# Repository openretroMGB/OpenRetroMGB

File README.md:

> Get ready to elevate your retro gaming experience with **OpenretroMGB** - the open-source, modular gaming board that lets you customize your gameplay. Our upcoming campaign will offer exclusive rewards and perks, so don't miss out on your chance to join the retro gaming revolution. Stay tuned for more details and be part of the community that's bringing back the best of the past with the power of the future!

## Overview

**OpenretroMGB** is a new open-source ***M***odular ***G***aming ***B***oard designed for gamers and hobbyists alike. Based on the popular Retro ESP32, this compact and portable board is compatible with Game Boy Pocket form factor and allows customers to either use the prebuilt ESP32 cartridge or design their own. With an easy-to-use modular design, gamers can customize their gaming experience by swapping out cartridges that feature different games or hardware functionalities. OpenretroMGB offers an affordable and accessible way to create and enjoy retro-style games with modern features, making it perfect for enthusiasts, hobbyists, and anyone looking for a fun, retro gaming experience.

**OpenretroMGB** is certified unde Open Source Hardware as OSHWA UID [CA000028](https://certification.oshwa.org/ca000028.html) with CC-BY-SA-4.0 licensing

## Features
- [x] Cartridge slot
- [x] 2.6" daylight IPS screen
- [x] Volume and brightness control
- [x] LiPo battery charging and protection circuitry
- [x] Stereo chip and headphone jack
- [x] Drop-in compatibility with Game Boy Pocket shell
- [x] Modular design
- [x] USB Data Lines
- [x] Open source

### Have your say

Join our discussions. Cast your vote in our [polls](https://github.com/openretroMGB/OpenRetroMGB/discussions/categories/polls)

## Gallery

#### Retro ESP32 Cart

#### Arduino *ATmega32U4* Cart

#### USB C Data Lines

# What will you build?

## Trusted Creators
> Celebrating 10 Years

Over the past 10 years, we have proudly established ourselves as a trusted creator and innovator in the realm of handheld retro gaming. From our early ventures with Arduino and Atmega microcontrollers to our exploration of cutting-edge technologies like ESP32 and Raspberry Pi, our journey has been driven by a relentless pursuit of innovation. With each step, we have strived to enhance the gaming experience for retro enthusiasts. Our Game Boy Pocket PCB embodies our dedication to quality, reliability, and creativity. It represents a culmination of years of expertise, resulting in a product that seamlessly blends the nostalgia of classic gaming with the power and possibilities of modern technology. As we celebrate this milestone, we extend our gratitude to our loyal customers and supporters, who have played an instrumental role in our growth and success. Looking ahead, we remain committed to pushing boundaries, embracing new advancements, and delivering unforgettable gaming experiences to enthusiasts around the world.

## Authors

* **Eugene Yevhen Andruszczenko** - *Initial and Ongoing Work* - [32teeth](https://github.com/32teeth)

### License

This project is licensed under the Creative Commons Attribution Share Alike 4.0 International - see the [LICENSE.md](LICENSE.md) file for details

## Support
> Although we do this for 💕 of 🕹️<br/>
> **We Also Like Coffee!** <br/>
> *Please Consider Supporting* <br/>

Did you know, you can support us in a few way? We offer multiple sposorship tiers, with different rewards!

Take a *look*.
See what *fits*.

**Thank You**

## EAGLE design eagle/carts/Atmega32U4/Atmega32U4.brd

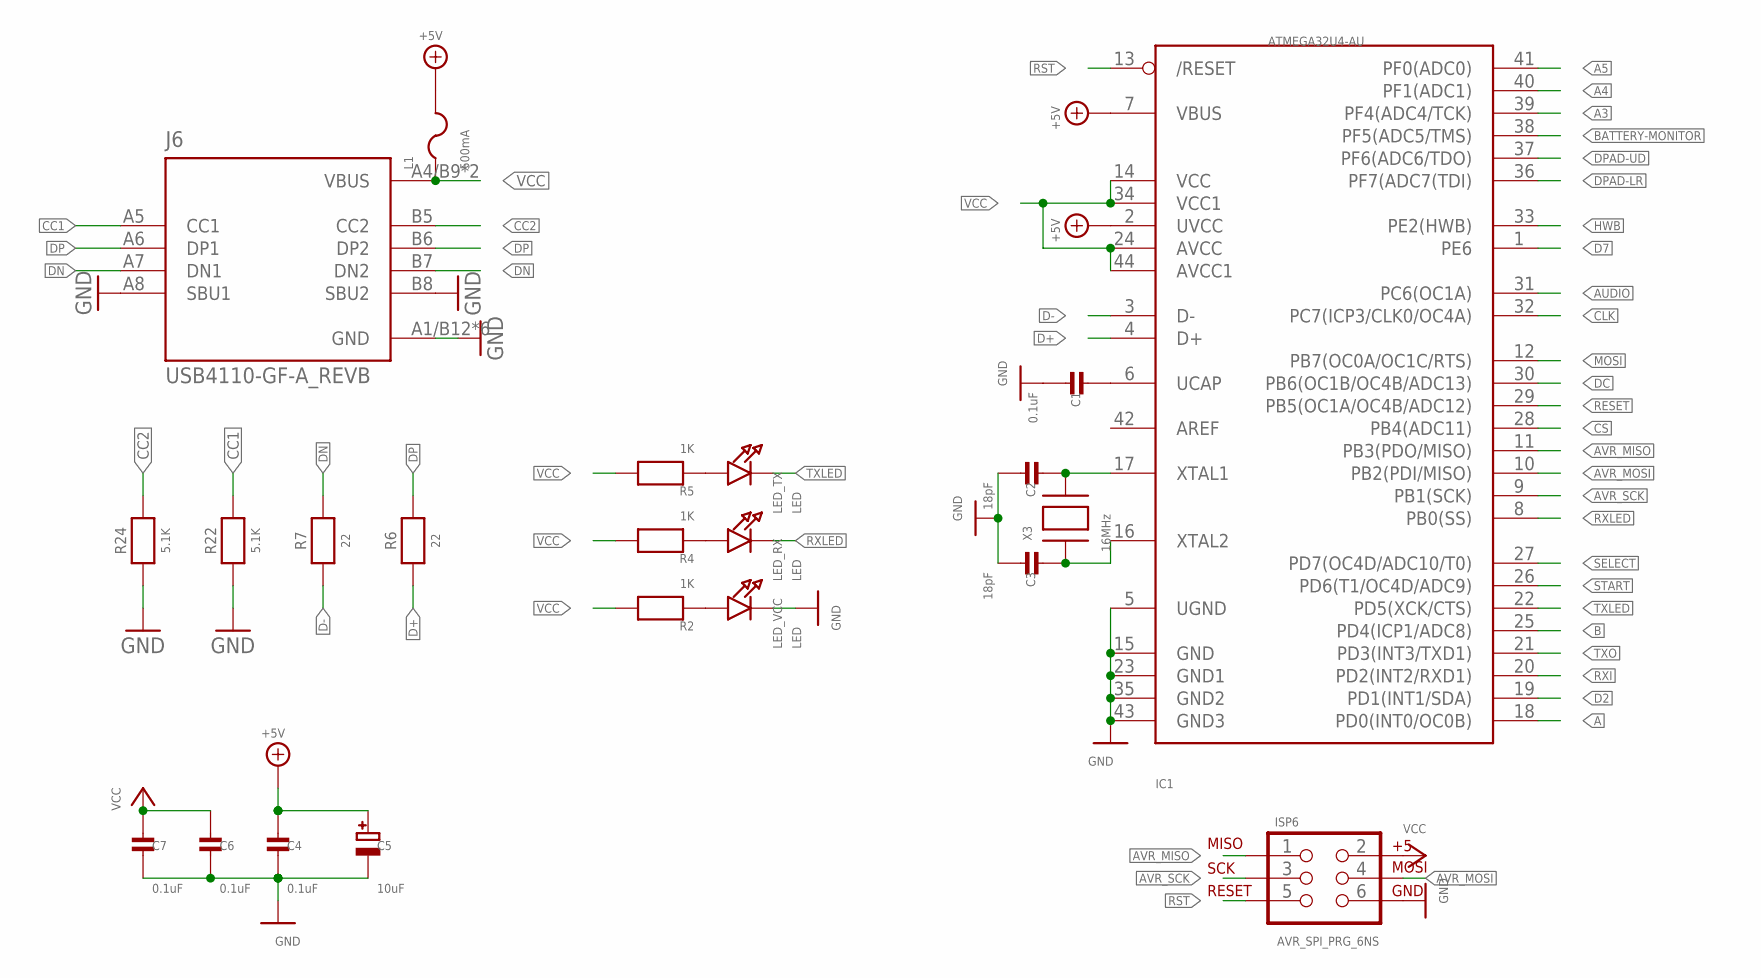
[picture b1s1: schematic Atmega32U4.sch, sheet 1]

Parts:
C1, C4, C6, C7: 0.1uF; 0603-MINI-CAP
C2, C3: 18pF; 0603-MINI-CAP
C5: 10uF; EIA3216-18/A-W
IC1: ATMEGA32U4-AU; TQFP44
ISP6: AVR_SPI_PRG_6NS; 2X3-NS
J6: USB4110-GF-A_REVB; GCT_USB4110-GF-A_REVB; MPN USB4105-GF-A
L1: 500mA; R1206
LED_RX: LED; CHIPLED_0603
LED_TX: LED; CHIPLED_0603
LED_VCC: LED; CHIPLED_0603
R2, R4, R5: 1K; 0603-MINI
R6, R7: 22; 0603-MINI; MPN ERJ-3EKF22R0V
R22, R24: 5.1K; 0603-MINI; MPN ERJ-PA3F5101V
X3: 16MHz; NX5032

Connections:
+5V: C4.1, C5.+, IC1.2 (UVCC), IC1.7 (VBUS), L1.2
A: IC1.18 (PD0(INT0/OC0B)); also elsewhere on the board
A3: IC1.39 (PF4(ADC4/TCK))
A4: IC1.40 (PF1(ADC1))
A5: IC1.41 (PF0(ADC0))
AUDIO: IC1.31 (PC6(OC1A)); also elsewhere on the board
AVR_MISO: IC1.11 (PB3(PDO/MISO)), ISP6.1
AVR_MOSI: IC1.10 (PB2(PDI/MISO)), ISP6.4
AVR_SCK: IC1.9 (PB1(SCK)), ISP6.3
B: IC1.25 (PD4(ICP1/ADC8)); also elsewhere on the board
BATTERY-MONITOR: IC1.38 (PF5(ADC5/TMS)); also elsewhere on the board
CC1: J6.A5 (CC1), R22.2
CC2: J6.B5 (CC2), R24.2
CLK: IC1.32 (PC7(ICP3/CLK0/OC4A)); also elsewhere on the board
CS: IC1.28 (PB4(ADC11)); also elsewhere on the board
D2: IC1.19 (PD1(INT1/SDA))
D7: IC1.1 (PE6)
D+: IC1.4 (D+), R6.1
D-: IC1.3 (D-), R7.1
DC: IC1.30 (PB6(OC1B/OC4B/ADC13)); also elsewhere on the board
DN: J6.A7 (DN1), J6.B7 (DN2), R7.2
DP: J6.A6 (DP1), J6.B6 (DP2), R6.2
DPAD-LR: IC1.36 (PF7(ADC7(TDI)); also elsewhere on the board
DPAD-UD: IC1.37 (PF6(ADC6/TDO)); also elsewhere on the board
GND: C1.2, C2.2, C3.2, C4.2, C5.-, C6.2, C7.2, IC1.5 (UGND), IC1.15 (GND), IC1.23 (GND1), IC1.35 (GND2), IC1.43 (GND3), ISP6.6, J6.A1/B12 (GND), J6.A8 (SBU1), J6.B1/A12 (GND), J6.B8 (SBU2), J6.S1 (GND), J6.S2 (GND), J6.S3 (GND), J6.S4 (GND), LED_VCC.C, R22.1, R24.1; also elsewhere on the board
HWB: IC1.33 (PE2(HWB))
MOSI: IC1.12 (PB7(OC0A/OC1C/RTS)); also elsewhere on the board
unnamed: LED_VCC.A, R2.1
unnamed: C1.1, IC1.6 (UCAP)
unnamed: LED_RX.A, R4.1
unnamed: LED_TX.A, R5.1
unnamed: C2.1, IC1.17 (XTAL1), X3.P$2
unnamed: C3.1, IC1.16 (XTAL2), X3.P$1
RESET: IC1.29 (PB5(OC1A/OC4B/ADC12)); also elsewhere on the board
RST: IC1.13 (/RESET), ISP6.5
RXI: IC1.20 (PD2(INT2/RXD1))
RXLED: IC1.8 (PB0(SS)), LED_RX.C
SELECT: IC1.27 (PD7(OC4D/ADC10/T0)); also elsewhere on the board
START: IC1.26 (PD6(T1/OC4D/ADC9)); also elsewhere on the board
TXLED: IC1.22 (PD5(XCK/CTS)), LED_TX.C
TXO: IC1.21 (PD3(INT3/TXD1))
VCC: C6.1, C7.1, IC1.14 (VCC), IC1.24 (AVCC), IC1.34 (VCC1), IC1.44 (AVCC1), ISP6.2, J6.A4/B9 (VBUS), J6.B4/A9 (VBUS), L1.1, R2.2, R4.2, R5.2; also elsewhere on the board

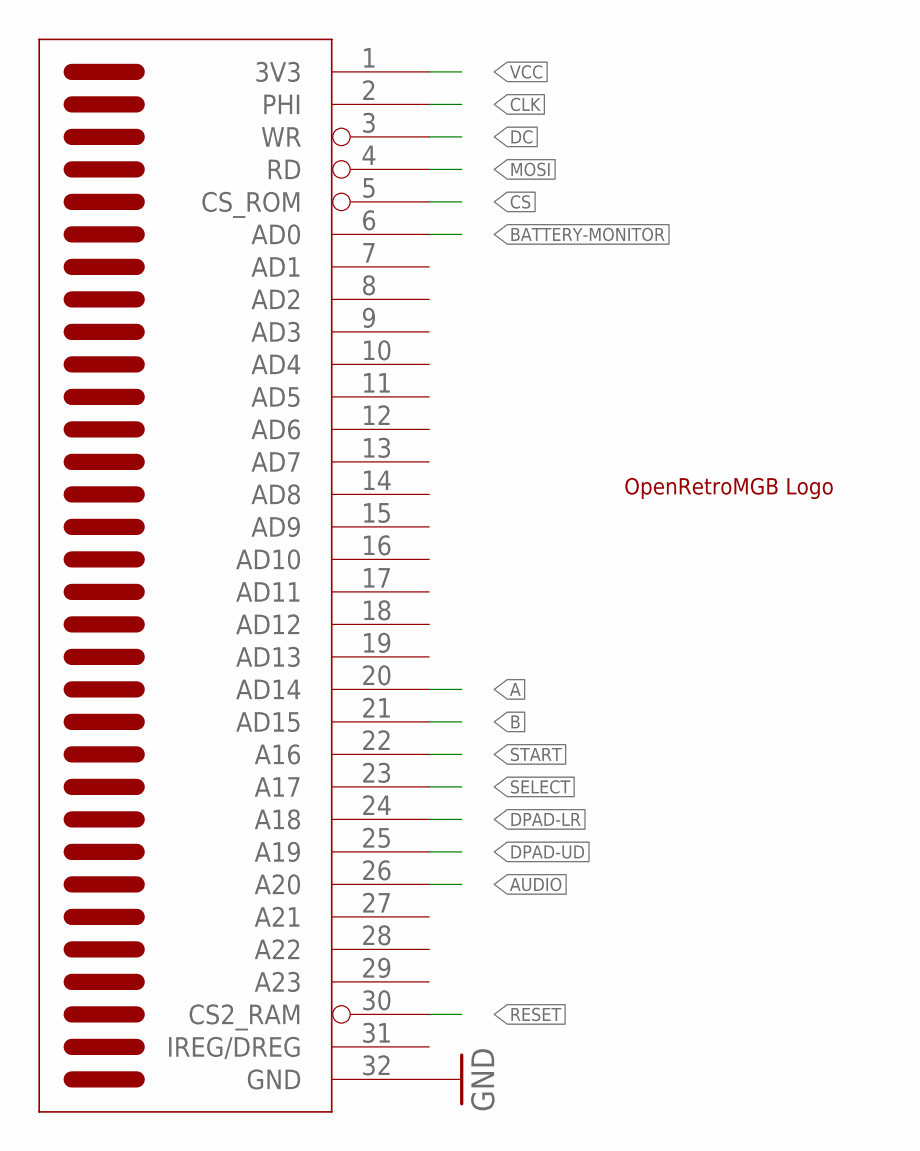
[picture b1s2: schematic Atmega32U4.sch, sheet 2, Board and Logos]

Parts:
U$1: OPENRETROMGB; OPENRETROMBG
U$2: GBA_CARTLARGE; GBCART

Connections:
A: U$2.20 (AD14); also elsewhere on the board
AUDIO: U$2.26 (A20); also elsewhere on the board
B: U$2.21 (AD15); also elsewhere on the board
BATTERY-MONITOR: U$2.6 (AD0); also elsewhere on the board
CLK: U$2.2 (PHI); also elsewhere on the board
CS: U$2.5 (CS_ROM); also elsewhere on the board
DC: U$2.3 (WR); also elsewhere on the board
DPAD-LR: U$2.24 (A18); also elsewhere on the board
DPAD-UD: U$2.25 (A19); also elsewhere on the board
GND: U$2.32 (GND); also elsewhere on the board
MOSI: U$2.4 (RD); also elsewhere on the board
RESET: U$2.30 (CS2_RAM); also elsewhere on the board
SELECT: U$2.23 (A17); also elsewhere on the board
START: U$2.22 (A16); also elsewhere on the board
VCC: U$2.1 (3V3); also elsewhere on the board

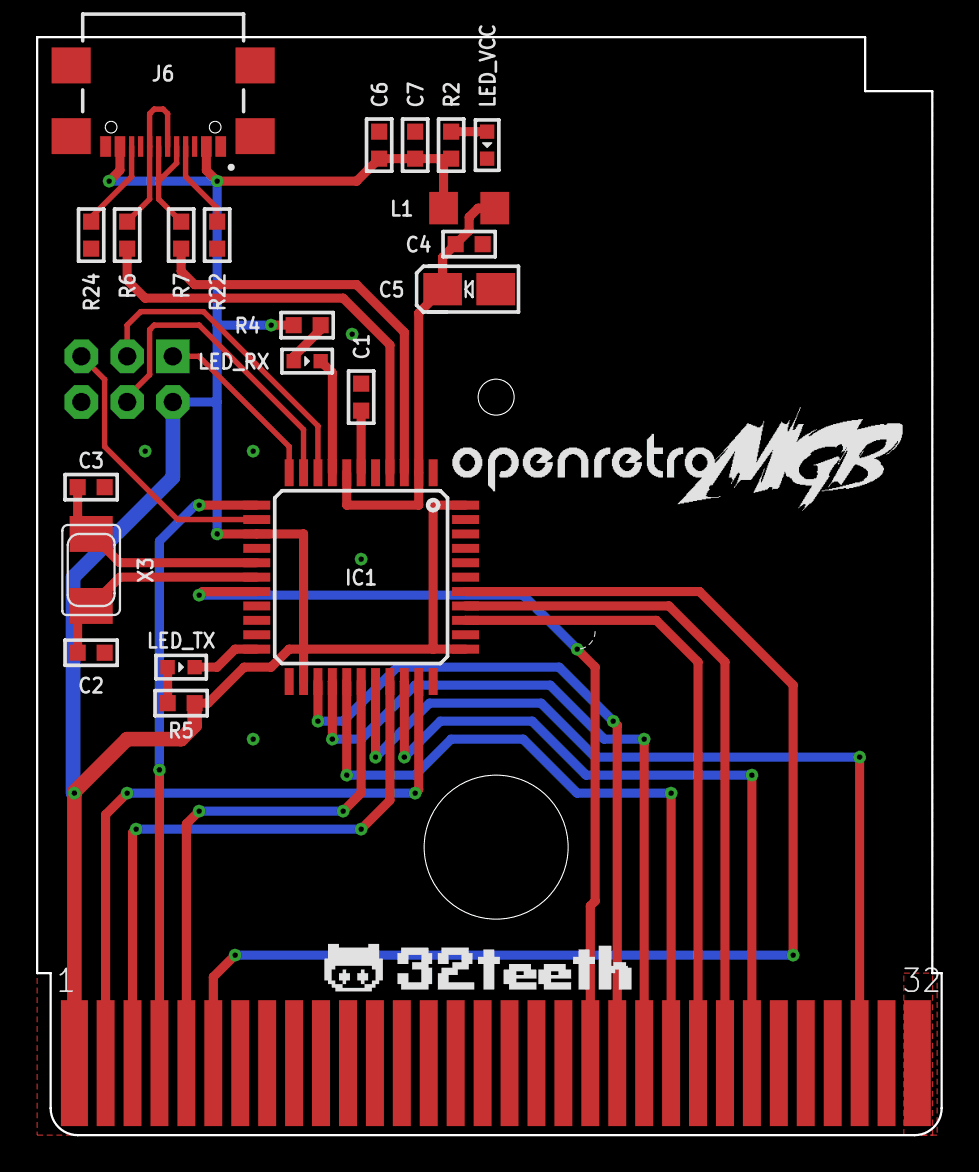
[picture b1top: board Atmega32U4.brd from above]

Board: 2 copper layers, 50.2 x 61.0 mm, 24 parts (0 on the bottom side), 34 nets.

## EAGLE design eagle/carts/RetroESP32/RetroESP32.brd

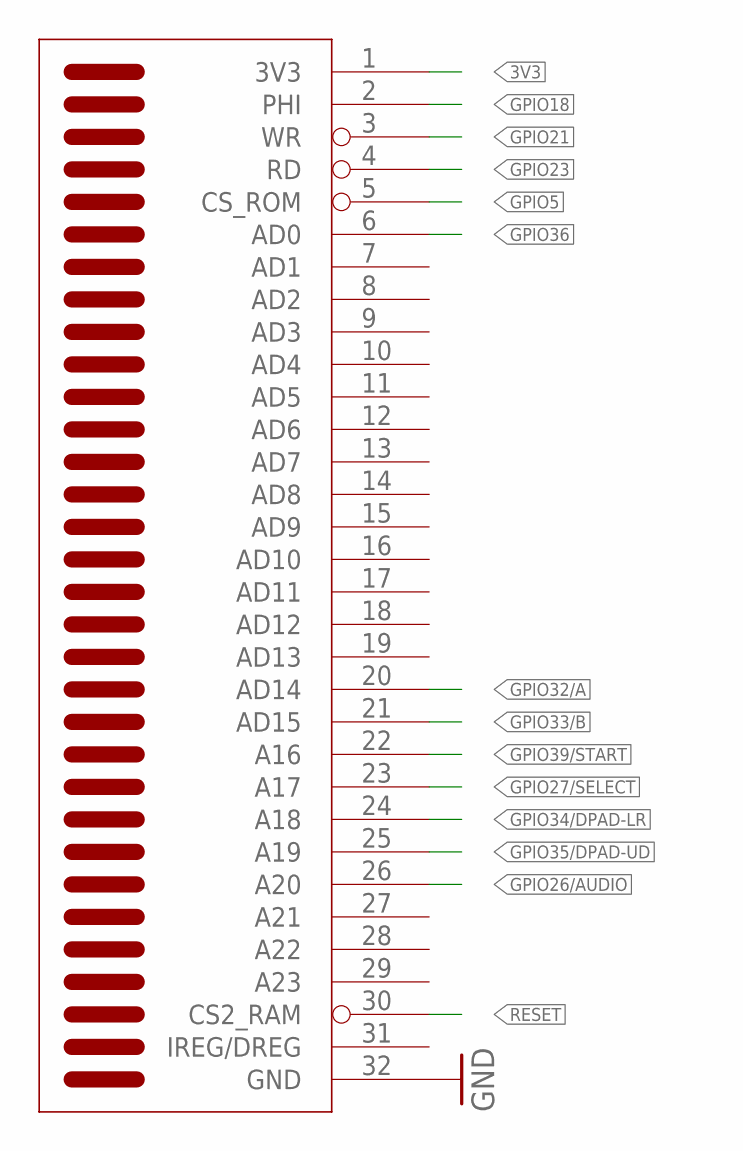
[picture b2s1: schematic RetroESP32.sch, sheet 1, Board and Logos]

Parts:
U$2: GBA_CARTLARGE; GBCART

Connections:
3V3: U$2.1 (3V3); also elsewhere on the board
GND: U$2.32 (GND); also elsewhere on the board
GPIO5: U$2.5 (CS_ROM); also elsewhere on the board
GPIO18: U$2.2 (PHI); also elsewhere on the board
GPIO21: U$2.3 (WR); also elsewhere on the board
GPIO23: U$2.4 (RD); also elsewhere on the board
GPIO26/AUDIO: U$2.26 (A20); also elsewhere on the board
GPIO27/SELECT: U$2.23 (A17); also elsewhere on the board
GPIO32/A: U$2.20 (AD14); also elsewhere on the board
GPIO33/B: U$2.21 (AD15); also elsewhere on the board
GPIO34/DPAD-LR: U$2.24 (A18); also elsewhere on the board
GPIO35/DPAD-UD: U$2.25 (A19); also elsewhere on the board
GPIO36: U$2.6 (AD0); also elsewhere on the board
GPIO39/START: U$2.22 (A16); also elsewhere on the board
RESET: U$2.30 (CS2_RAM); also elsewhere on the board

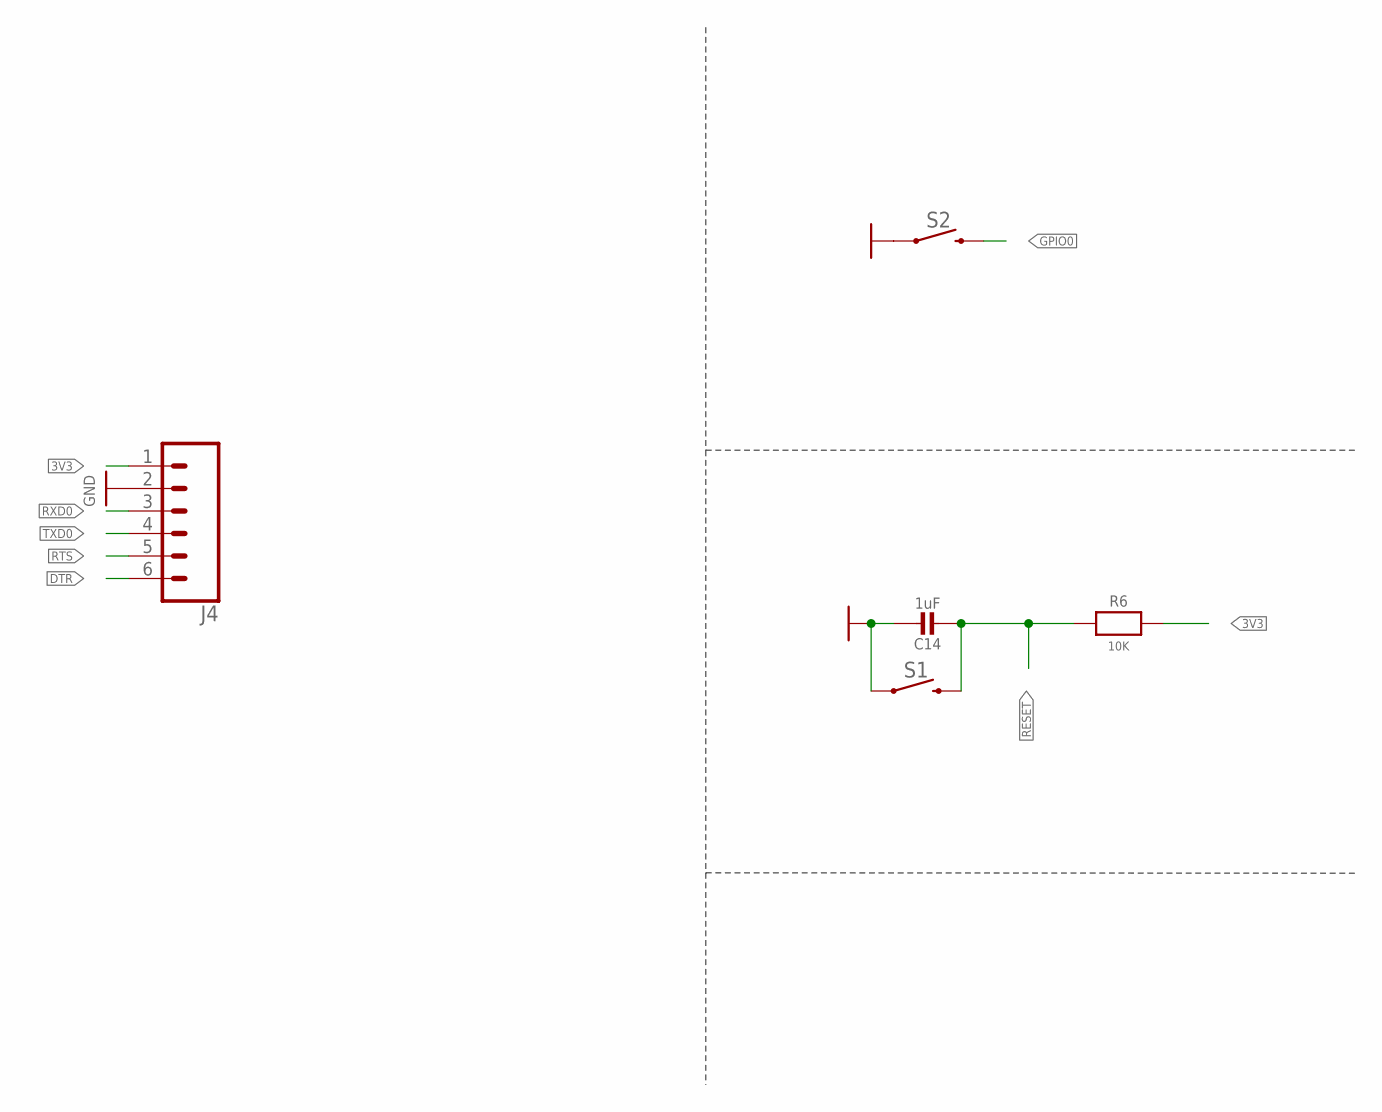
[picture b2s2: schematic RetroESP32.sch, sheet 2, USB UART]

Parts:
C14: 1uF; 0603-MINI-CAP; MPN CL10A105KP8NNNC
J4: CONN_06NO_SILK_NO_POP; 1X06_NO_SILK
R6: 10K; 0603-MINI; MPN ERJ-PA3J103V
S1, S2: SWITCHES_MOMENTARY-SWITCH-SPST-SMD-4.6X2.8MM; SWITCHES_TACTILE_SWITCH_SMD_4.6X2.8MM; MPN KMR221GLFS

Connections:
3V3: J4.1, R6.2; also elsewhere on the board
DTR: J4.6; also elsewhere on the board
GND: C14.1, J4.2, S1.1, S1.2 (1), S2.1, S2.2 (1); also elsewhere on the board
GPIO0: S2.3 (2), S2.4 (2); also elsewhere on the board
RESET: C14.2, R6.1, S1.3 (2), S1.4 (2); also elsewhere on the board
RTS: J4.5; also elsewhere on the board
RXD0: J4.3; also elsewhere on the board
TXD0: J4.4; also elsewhere on the board

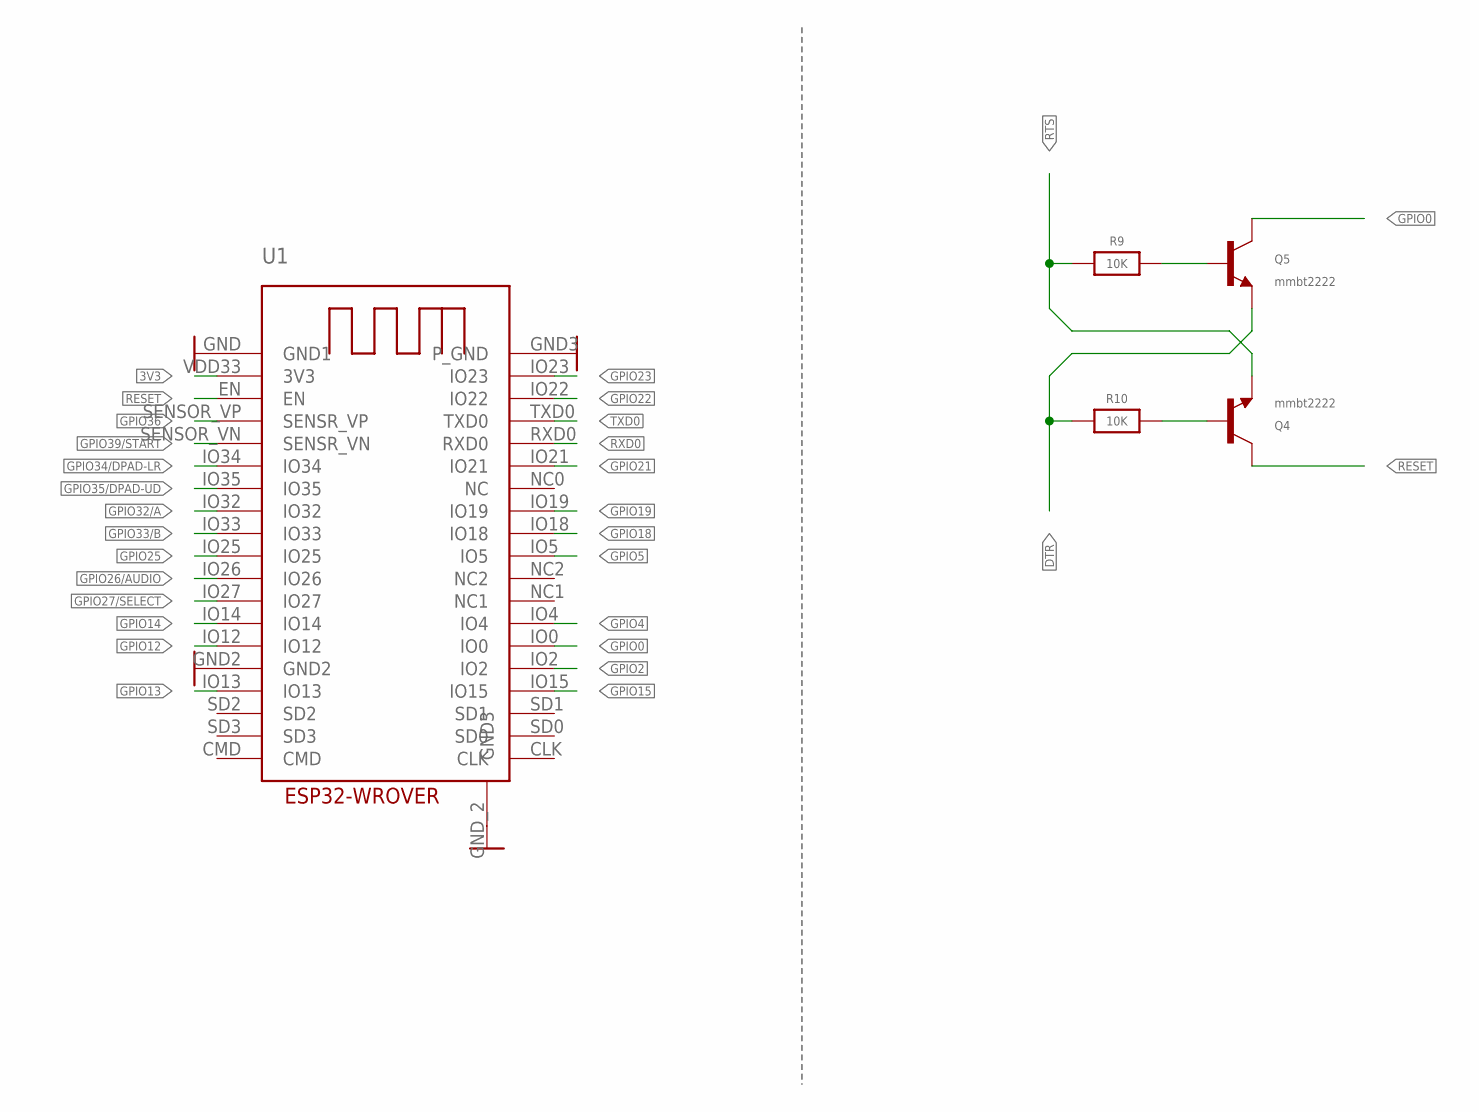
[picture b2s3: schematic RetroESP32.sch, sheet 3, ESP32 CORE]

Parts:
Q4, Q5: mmbt2222; SOT23-3; MPN MMBT2222A-7-F
R9, R10: 10K; 0603-MINI; MPN ERJ-PA3J103V
U1: ESP32-WROVER_ESP32-WROVER; MPN ESP32-WROVER (16MB)

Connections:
3V3: U1.VDD33 (3V3); also elsewhere on the board
DTR: Q5.2 (E), R10.1; also elsewhere on the board
GND: U1.GND (GND1), U1.GND2, U1.GND3 (P_GND), U1.GND_2 (GND3); also elsewhere on the board
GPIO0: Q5.3 (C), U1.IO0; also elsewhere on the board
GPIO2: U1.IO2
GPIO4: U1.IO4
GPIO5: U1.IO5; also elsewhere on the board
GPIO12: U1.IO12
GPIO13: U1.IO13
GPIO14: U1.IO14
GPIO15: U1.IO15
GPIO18: U1.IO18; also elsewhere on the board
GPIO19: U1.IO19; also elsewhere on the board
GPIO21: U1.IO21; also elsewhere on the board
GPIO22: U1.IO22; also elsewhere on the board
GPIO23: U1.IO23; also elsewhere on the board
GPIO25: U1.IO25
GPIO26/AUDIO: U1.IO26; also elsewhere on the board
GPIO27/SELECT: U1.IO27; also elsewhere on the board
GPIO32/A: U1.IO32; also elsewhere on the board
GPIO33/B: U1.IO33; also elsewhere on the board
GPIO34/DPAD-LR: U1.IO34; also elsewhere on the board
GPIO35/DPAD-UD: U1.IO35; also elsewhere on the board
GPIO36: U1.SENSOR_VP (SENSR_VP); also elsewhere on the board
GPIO39/START: U1.SENSOR_VN (SENSR_VN); also elsewhere on the board
RESET: Q4.3 (C), U1.EN; also elsewhere on the board
RST-RES: Q4.1 (B), R10.2
RTS: Q4.2 (E), R9.1; also elsewhere on the board
RTS-RES: Q5.1 (B), R9.2
RXD0: U1.RXD0; also elsewhere on the board
TXD0: U1.TXD0; also elsewhere on the board

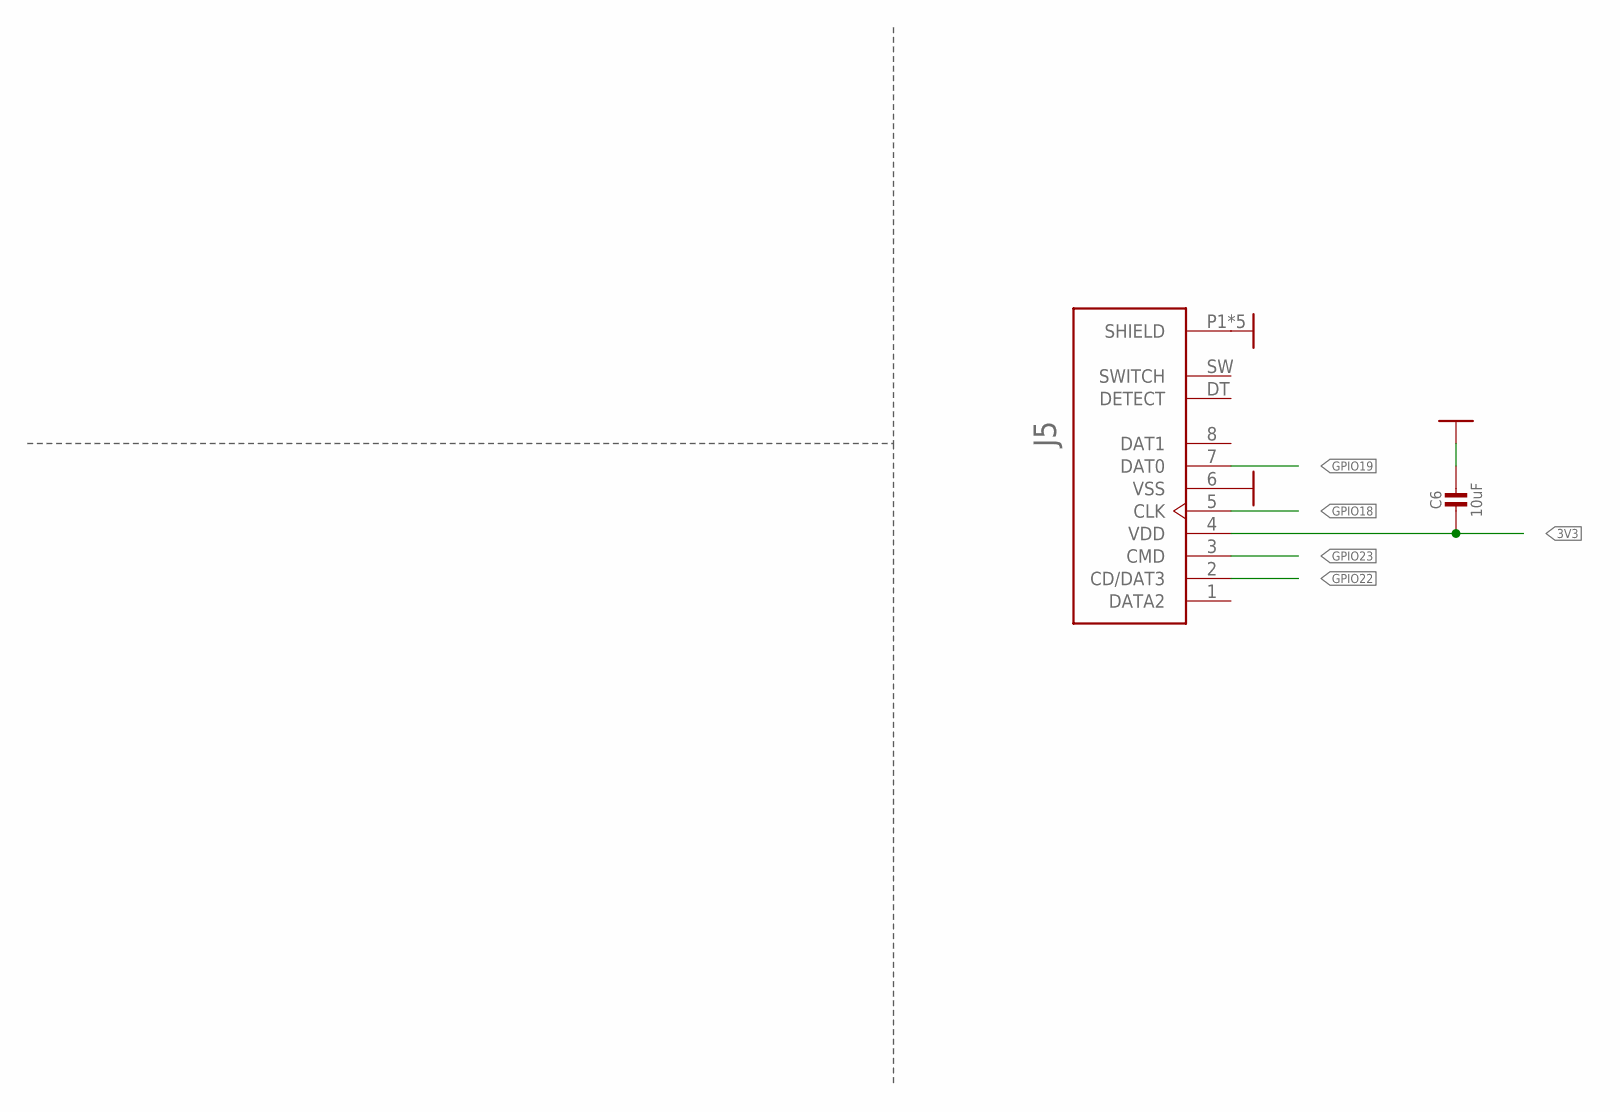
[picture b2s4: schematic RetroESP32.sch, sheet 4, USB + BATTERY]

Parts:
C6: 10uF; 0603-MINI-CAP; MPN CL10A106MP8NNNC
J5: 503182-1852_503182-1852; 503182-1852_MOLEX_503182-1852; MPN 5031821852

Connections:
3V3: C6.2, J5.4 (VDD); also elsewhere on the board
GND: C6.1, J5.6 (VSS), J5.P1 (SHIELD), J5.P2 (SHIELD), J5.P3 (SHIELD), J5.P4 (SHIELD), J5.P5 (SHIELD); also elsewhere on the board
GPIO18: J5.5 (CLK); also elsewhere on the board
GPIO19: J5.7 (DAT0); also elsewhere on the board
GPIO22: J5.2 (CD/DAT3); also elsewhere on the board
GPIO23: J5.3 (CMD); also elsewhere on the board

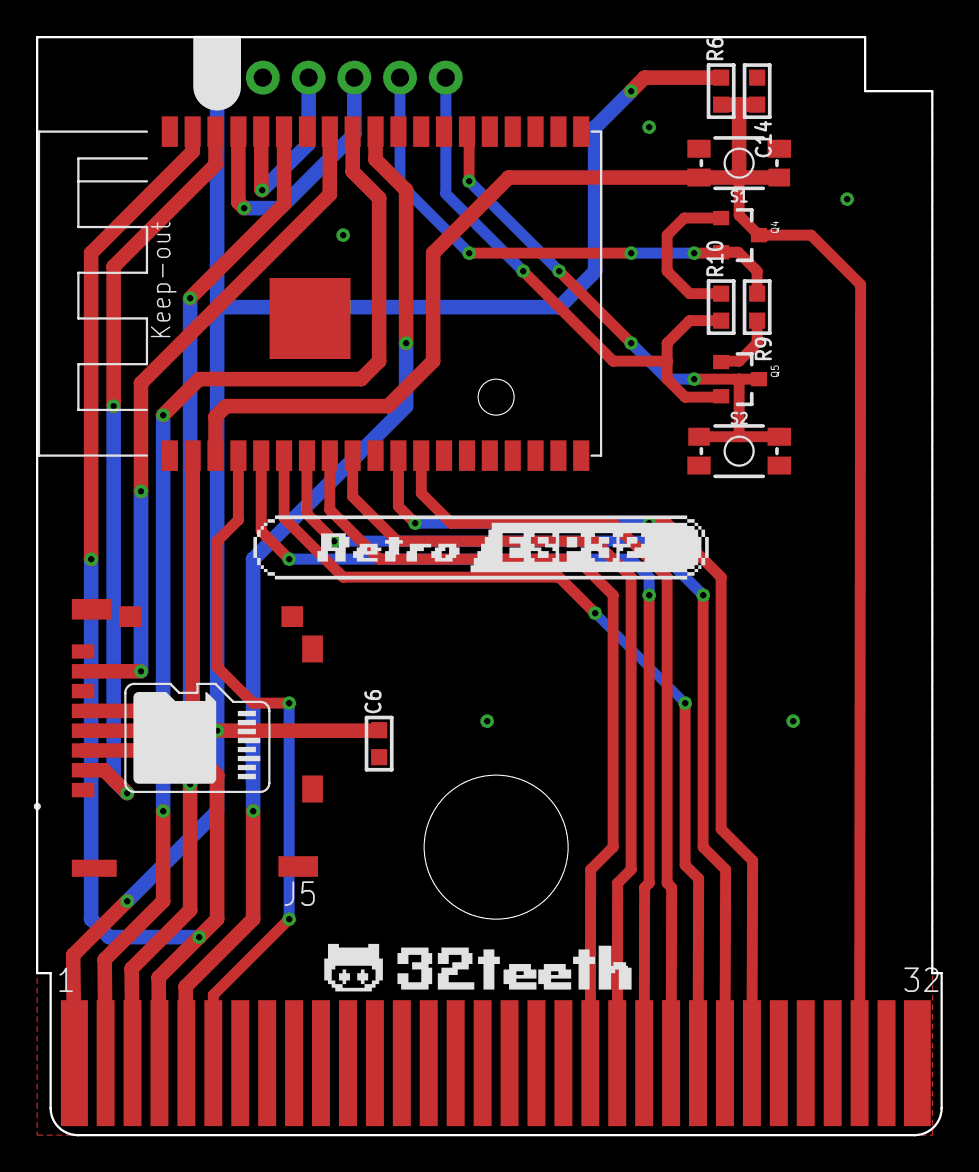
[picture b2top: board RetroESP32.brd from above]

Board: 2 copper layers, 50.2 x 61.0 mm, 13 parts (0 on the bottom side), 24 nets.

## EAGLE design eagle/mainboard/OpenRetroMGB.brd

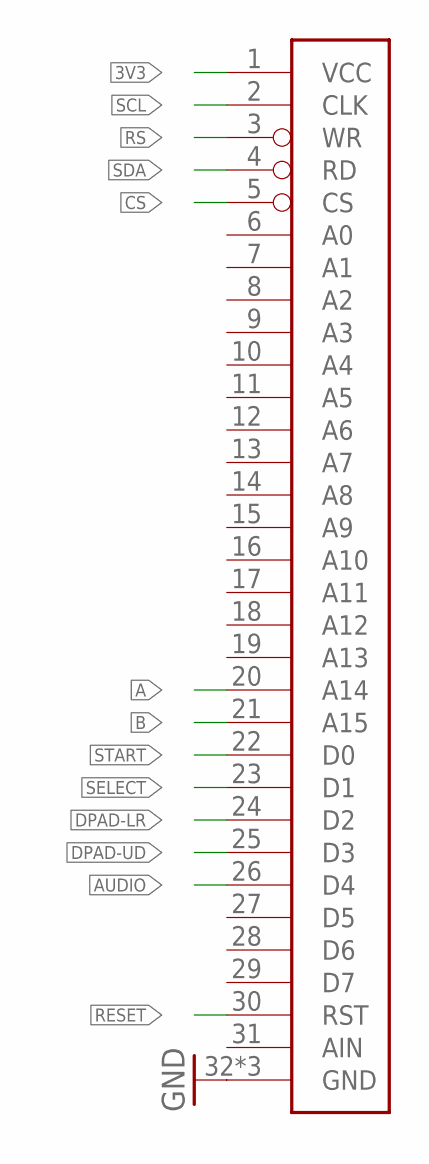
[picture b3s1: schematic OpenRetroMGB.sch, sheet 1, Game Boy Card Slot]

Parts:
U$2: GB-CARTRIDGE-SLOTV2; GB-CARTRIDGE-SLOT-2

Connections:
3V3: U$2.1 (VCC); also elsewhere on the board
A: U$2.20 (A14); also elsewhere on the board
AUDIO: U$2.26 (D4); also elsewhere on the board
B: U$2.21 (A15); also elsewhere on the board
CS: U$2.5 (CS); also elsewhere on the board
DPAD-LR: U$2.24 (D2); also elsewhere on the board
DPAD-UD: U$2.25 (D3); also elsewhere on the board
GND: U$2.32 (GND), U$2.PAD1 (GND), U$2.PAD2 (GND); also elsewhere on the board
RESET: U$2.30 (RST); also elsewhere on the board
RS: U$2.3 (WR); also elsewhere on the board
SCL: U$2.2 (CLK); also elsewhere on the board
SDA: U$2.4 (RD); also elsewhere on the board
SELECT: U$2.23 (D1); also elsewhere on the board
START: U$2.22 (D0); also elsewhere on the board

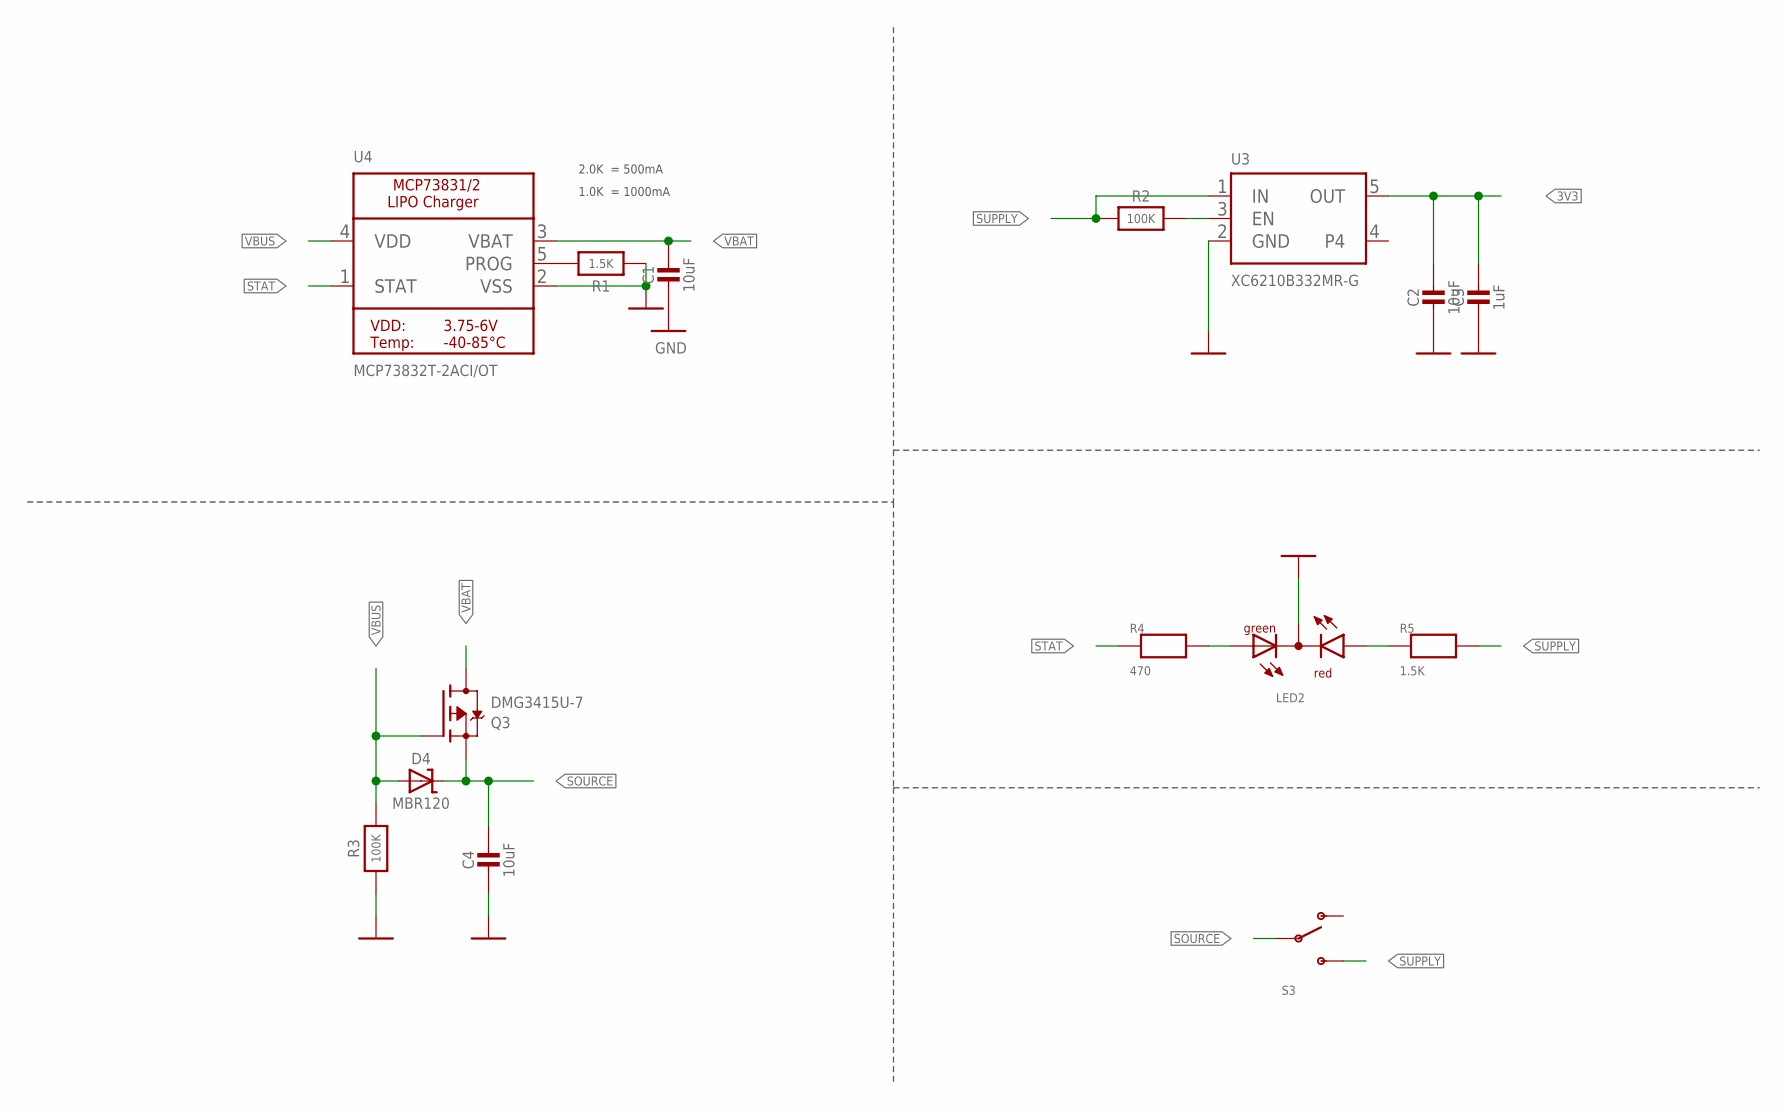
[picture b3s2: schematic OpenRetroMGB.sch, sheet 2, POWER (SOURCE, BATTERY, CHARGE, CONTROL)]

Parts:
C1, C2, C4: 10uF; 0603-MINI-CAP; MPN CL10A106MP8NNNC
C3: 1uF; 0603-MINI-CAP; MPN CL10A105KP8NNNC
D4: MBR120; SOD-123; MPN MBR120LSFT1G
LED2: LED_L-115WEGW-CA; LED_DUOLED-A-3MM; MPN SSL-LX3059IGW
Q3: DMG3415U-7; SOT23-R; MPN DMG3415U-7
R1, R5: 1.5K; 0603-MINI; MPN ERJ-PA3J152V
R2, R3: 100K; 0603-MINI; MPN ERJ-PA3J104V
R4: 470; 0603-MINI; MPN ERJ-PA3J471V
S3: RETIRED_SWITCH_SPDT; RETIRED_KPS-1290; MPN MA12RTR
U3: XC6210B332MR-G; SOT23-5; MPN XC6210B332MR-G
U4: MCP73832T-2ACI/OT; SOT23-5-1; MPN MCP73832T-2ACI/OT

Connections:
3V3: C2.1, C3.1, U3.5 (OUT); also elsewhere on the board
EN: R2.2, U3.3 (EN)
GND: C1.2, C2.2, C3.2, C4.2, LED2.2 (A), R1.1, R3.1, U3.2 (GND), U4.2 (VSS); also elsewhere on the board
POWER_LED: LED2.3 (CR), R5.1
PROG: R1.2, U4.5 (PROG)
SOURCE: C4.1, D4.C, Q3.2 (S), S3.P; also elsewhere on the board
STAT: R4.1, U4.1 (STAT)
STAT_LED: LED2.1 (CG), R4.2
SUPPLY: R2.1, R5.2, S3.S, U3.1 (IN); also elsewhere on the board
VBAT: C1.1, Q3.3 (D), U4.3 (VBAT); also elsewhere on the board
VBUS: D4.A, Q3.1 (G), R3.2, U4.4 (VDD); also elsewhere on the board

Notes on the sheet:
2.0K = 500mA
1.0K = 1000mA

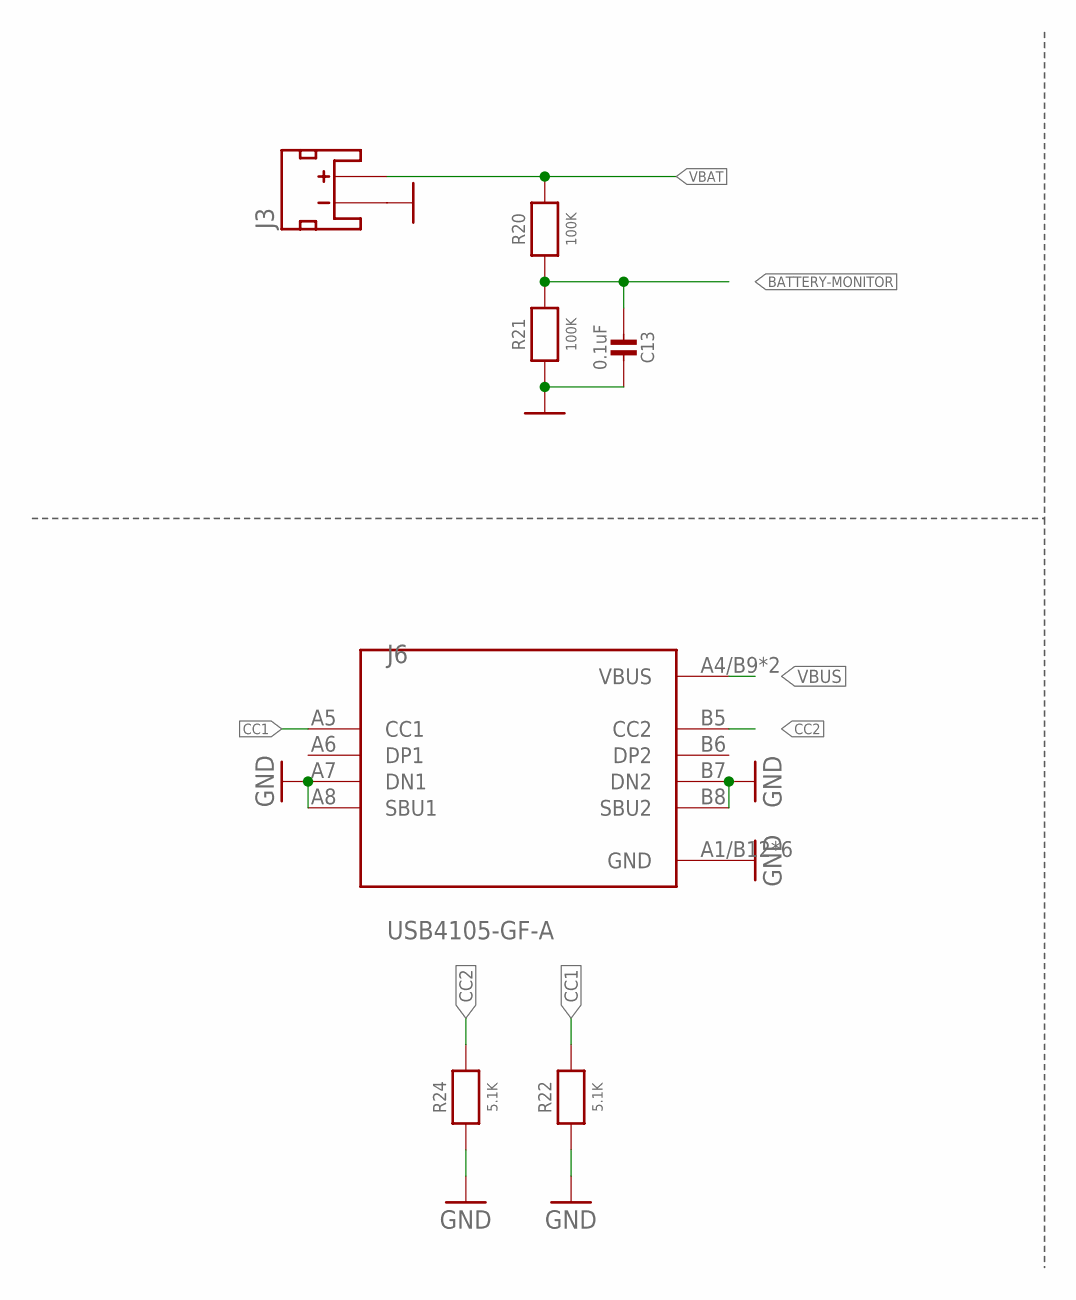
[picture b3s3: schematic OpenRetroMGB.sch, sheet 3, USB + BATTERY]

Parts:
C13: 0.1uF; 0603-MINI-CAP; MPN CL10B104KB8NNNC
J3: Batt Conn; JST-2-SMD; MPN S2B-PH-SM4-TB(LF)(SN)
J6: USB4105-GF-A; GCT_USB4105-GF-A; MPN USB4105-GF-A
R20, R21: 100K; 0603-MINI; MPN ERJ-PA3J104V
R22, R24: 5.1K; 0603-MINI; MPN ERJ-PA3F5101V

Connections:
BATTERY-MONITOR: C13.2, R20.1, R21.2
CC1: J6.A5 (CC1), R22.2
CC2: J6.B5 (CC2), R24.2
GND: C13.1, J3.1 (-), J6.A1/B12 (GND), J6.A7 (DN1), J6.A8 (SBU1), J6.B1/A12 (GND), J6.B7 (DN2), J6.B8 (SBU2), J6.G1 (GND), J6.G2 (GND), J6.G3 (GND), J6.G4 (GND), R21.1, R22.1, R24.1; also elsewhere on the board
VBAT: J3.2 (+), R20.2; also elsewhere on the board
VBUS: J6.A4/B9 (VBUS), J6.B4/A9 (VBUS); also elsewhere on the board

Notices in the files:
parts and their libraries:
SparkFun-PowerSymbols: Licensing: Creative Commons ShareAlike 4.0 International - https://creativecommons.org/licenses/by-sa/4.0
jrodrigo-gameboy: Creative Commons - Attribution and Share Alike 4.0 International - https://creativecommons.org/licenses/by-sa/4.0
